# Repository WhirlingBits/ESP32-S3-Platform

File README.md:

# ESP_Platform_Schematic

## Description
Schematics of basic ESP32-S3-WROOM platform with versatile power management
for 12V and 5V supply and microSD card slot.
The board offers 2 USB-C receptables, one connecting to a USB-2-UART converter
(CP2102) feeding the genuine UART0 on ESP32-S3 and another directly connecting
to the ESP32-S3's USB OTG port.

## Power Management
The board may be powered by one of the USB ports (VBUS) or with an external
power supply connected via BarrelJack. So altogether there are 3 possible sources of
power, USB (PGM), USB (Data) and Ext. To prevent any currents flowing from the
source with higher voltage to a source with lower voltage Schotty diodes with
low treshold have been implemented.

Thanx to the buck/boost capability of the LTC3111 used the external power input
voltage may supply a voltage between 3..15V.

Alternatively it is possible to use an external battery controller (e.g. Sparkfun
Babysitter) which is connected on J5 whereas J5.4 (+5VD) will be the input for the
controller and J5.1,2 the output.

## Wifi/BT module from Espressif
For the module we have chosen an ESP32-S3-WROOM-1 from Espressif with 8MByte
serial FLASH and 8MByte PSRAM (suffix -N8R8). ESP32-S3 is more powerful than
classical ESP32-D0WD as its using Dual Core Tensilica LX7 with an augmented 
instruction set supporting low level calculations for CNN processing (tinyML).
For precision of all time related processes there's an clock crystal (32kHz)
assembled.

And this is the real board:

## CAE System
Schematics and Layout have been developed using KiCAD 5.x version. You may
just download the complete repository to a folder inside your KiCAD project
directories to start using it.

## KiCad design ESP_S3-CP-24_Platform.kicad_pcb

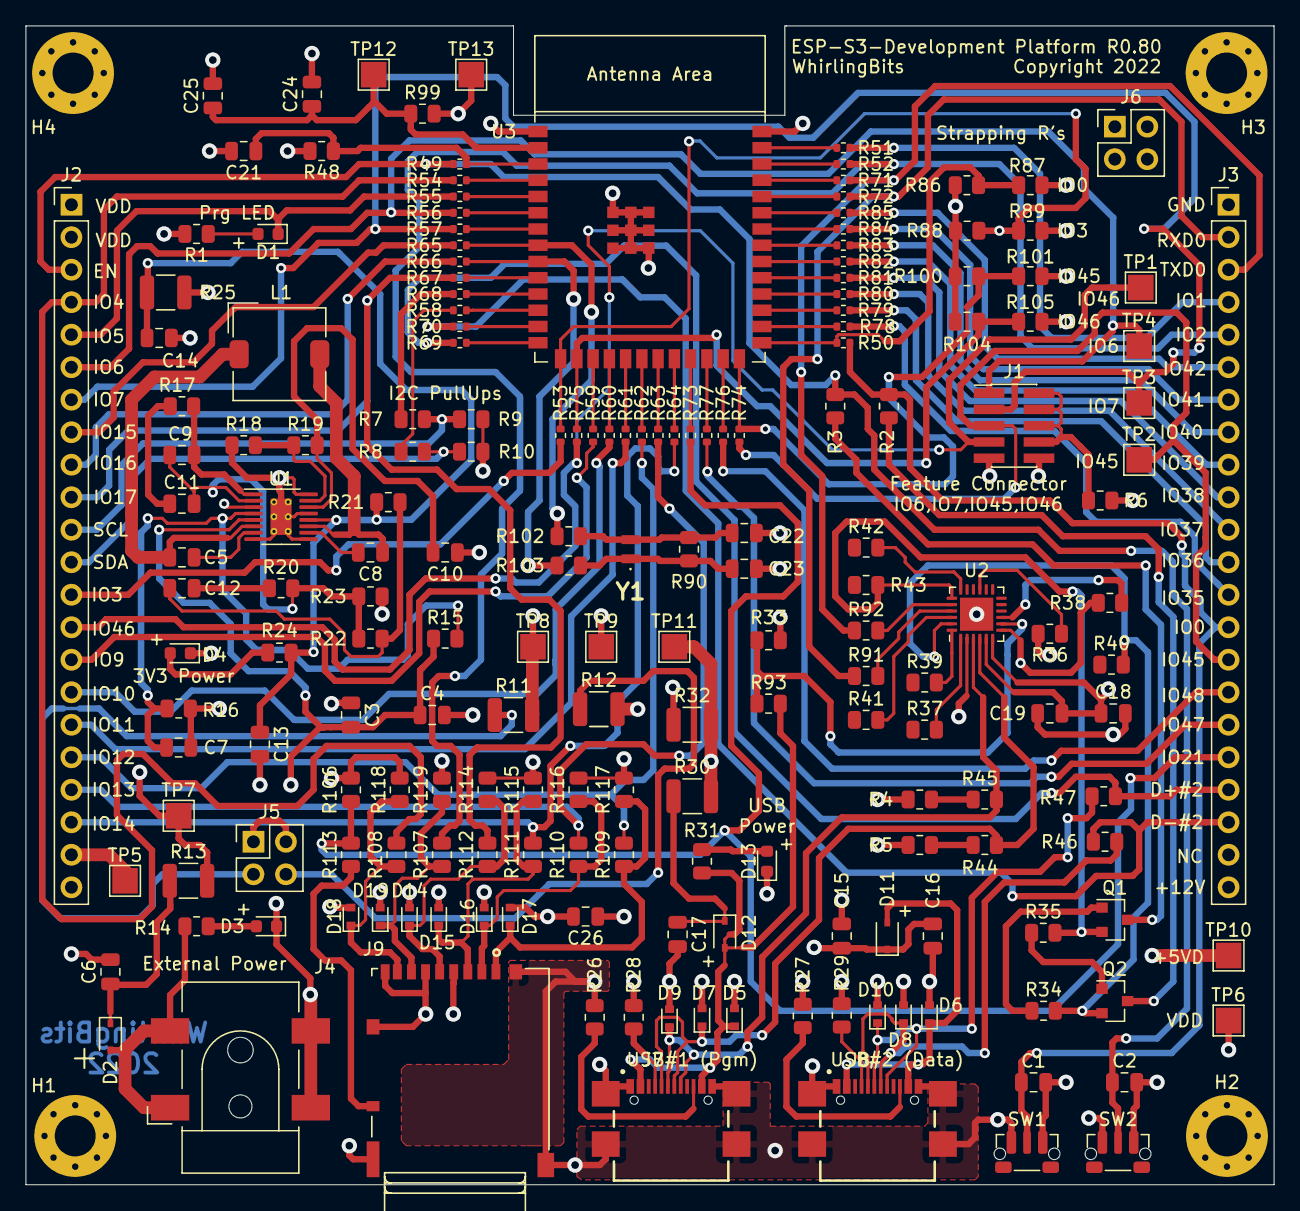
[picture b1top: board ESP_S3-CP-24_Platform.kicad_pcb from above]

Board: 4 copper layers, 97.5 x 90.6 mm, 193 parts (0 on the bottom side), 142 nets.

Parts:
C1: 0.1uF, 50V (DNP); C_0805_2012Metric
C2, C3, C5, C8, C15, C18, C21, C25: 0.1uF, 50V; C_0805_2012Metric
C4, C6: 47uF, 22V; C_0805_2012Metric
C7, C10, C14: 1uF, 16V; C_0805_2012Metric
C9: 22p; C_0805_2012Metric
C11: 1500p; C_0805_2012Metric
C12: 47p; C_0805_2012Metric
C13: 100uF, 6,3V; C_0805_2012Metric
C16, C17, C19: 4.7uF, 25V; C_0805_2012Metric
C22, C23: 12pF, 50V; C_0805_2012Metric
C24, C26: 22uF, 10V; C_0805_2012Metric
D1, D3, D4, D13: LTST-C191KRKT (Red); LED_0603_1608Metric
D2, D11, D12: BAT760-7; D_SOD-323
D5, D6, D7, D8, D9, D10, D14, D15, D16, D17, D18, D19: PESD15VW1BCSFYL; D_SOD-523
H1, H2, H3, H4: M3-L5-3.5; MountingHole_3.2mm_M3_Pad_Via
J1: Conn_02x05_Odd_Even; PinHeader_2x05_P1.27mm_Vertical_SMD
J2, J3: Conn_01x22 (DNP); PinHeader_1x22_P2.54mm_Vertical
J4: PJ-002AH-SMT-TR (Barrel Jack); BarrelJack_CLIFF_FC681465S_SMT_Horizontal
J5: Conn_02x02_Top_Bottom; PinHeader_2x02_P2.54mm_Vertical
J6: Conn_02x02_Top_Bottom (DNP); PinHeader_2x02_P2.54mm_Vertical
J7, J8: USB4110-GF-A_REVB; GCT_USB4110-GF-A_REVB
J9: DM3AT-SF-PEJM5; HRS_DM3AT-SF-PEJM5
L1: 10uH - SLF7032T-100M1R4-2PF; L_TDK_SLF7032
Q1, Q2: SS8050-G; SOT-23
R1: 1k8; R_0805_2012Metric
R2, R3, R6, R7, R8, R19, R37, R39, R40, R41, R42, R43, R91, R92, R99, R102, R103, R107, R108, R109, R110, R111, R112, R113: 0R; R_0805_2012Metric
R4, R5, R16: 1M (DNP); R_0805_2012Metric
R9, R10, R38: 1k; R_0805_2012Metric
R11, R12, R13, R25, R30, R32: 0R1; R_1210_3225Metric
R14, R26, R27, R28, R29, R88, R101: 5k1; R_0805_2012Metric
R15: 1M; R_0805_2012Metric
R17: 41,2k; R_0805_2012Metric
R18: 0R (DNP); R_0805_2012Metric
R20: 11,5k; R_0805_2012Metric
R21: 49R9; R_0805_2012Metric
R22: 845k; R_0805_2012Metric
R23: 261k; R_0805_2012Metric
R24: 1k5; R_0805_2012Metric
R31: 2k2; R_0805_2012Metric
R33: 43k; R_0805_2012Metric
R34, R35, R48, R106, R114, R115, R116, R117, R118, R119: 10k; R_0805_2012Metric
R36: 10k (DNP); R_0805_2012Metric
R44, R45, R46, R47: 22R; R_0805_2012Metric
R49, R50, R51, R52, R53, R54, R55, R56, R57, R58, R59, R60, R61, R62, R63, R64, R65, R66, R67, R68, R69, R70, R71, R72, R73, R74, R75, R76, R77, R78, R79, R80, R81, R82, R83, R84, R85: 22R; R_0402_1005Metric
R86, R87, R89, R100, R104, R105: 5k1 (DNP); R_0805_2012Metric
R90: 5.6M; R_0805_2012Metric
R93: 22k; R_0805_2012Metric
SW1, SW2: SKRTLAE010; SW_Push_1P1T-MP_NO_Horizontal_Alps_SKRTLAE010
TP1: T_IO46; TestPoint_Pad_2.0x2.0mm
TP2: T_IO45; TestPoint_Pad_2.0x2.0mm
TP3: T_IO7; TestPoint_Pad_2.0x2.0mm
TP4: T_IO6; TestPoint_Pad_2.0x2.0mm
TP5: +5VD; TestPoint_Pad_2.0x2.0mm
TP6, TP12: ESP-Power; TestPoint_Pad_2.0x2.0mm
TP7: +12V; TestPoint_Pad_2.0x2.0mm
TP8: Ext Voltage 12V; TestPoint_Pad_2.0x2.0mm
TP9: 3V3; TestPoint_Pad_2.0x2.0mm
TP10: USB Voltage; TestPoint_Pad_2.0x2.0mm
TP11: USB Vltge #2; TestPoint_Pad_2.0x2.0mm
TP13: VDD33; TestPoint_Pad_2.0x2.0mm
U1: LTC3111EMSEPBF; MSOP-16-1EP_3x4.039mm_P0.5mm_EP1.651x2.845mm_ThermalVias
U2: CP2102N-A02-GQFN24; QFN-24-1EP_4x4mm_P0.5mm_EP2.6x2.6mm
U3: ESP32-S3-WROOM-1
Y1: XTAL 32,678kHz (C20S-12.5PF20PPM); SC20S125PF20PPM

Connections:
+5VD: J2.21, R12.2, R30.2, R32.2, TP5.1, TP10.1, TP11.1
+12V: J3.22, R11.2, R13.2, TP7.1, TP8.1
/CP_EN: Q1.3, R3.2
/CP_IO0: Q2.3, R2.2
/Espressif Developer PLatform - uSDCard/SD_DET: J9.SWA, R113.1
/Espressif Developer PLatform - uSDCard/SD_HOST_CLK: D14.1, J9.5, R112.1, R114.1
/Espressif Developer PLatform - uSDCard/SD_HOST_CMD: D15.1, J9.3, R111.1, R115.1
/Espressif Developer PLatform - uSDCard/SD_HOST_D0: D19.1, J9.7, R107.1, R119.1
/Espressif Developer PLatform - uSDCard/SD_HOST_D1: D18.1, J9.8, R108.1, R118.1
/Espressif Developer PLatform - uSDCard/SD_HOST_D2: D17.1, J9.1, R109.1, R117.1
/Espressif Developer PLatform - uSDCard/SD_HOST_D3: D16.1, J9.2, R110.1, R116.1
/Espressif Developer Platform - Interfaces/USB-D+#2: D10.1, J8.A6, J8.B6, R47.2
/Espressif Developer Platform - Interfaces/USB-D-#2: D8.1, J8.A7, J8.B7, R46.2
/Espressif Developer Platform - Interfaces/USB_VBUS#2: D6.1, D11.2, J8.A4/B9, J8.B4/A9
/Espressif Developer Platform - Modules/32K_XN: R66.1, R103.1, U3.9
/Espressif Developer Platform - Modules/32K_XP: R65.1, R102.1, U3.8
/Espressif Developer Platform - Modules/ESP-Power: C24.1, C25.1, R99.1, TP12.1, U3.2
/Espressif Developer Platform - Modules/ESP_EN: C21.1, R48.1, R49.1, U3.3
/Espressif Developer Platform - Modules/IO_0: R50.1, R86.1, R87.2, U3.27
/Espressif Developer Platform - Modules/IO_1: R51.1, U3.39
/Espressif Developer Platform - Modules/IO_2: R52.1, U3.38
/Espressif Developer Platform - Modules/IO_3: R53.1, R88.1, R89.2, U3.15
/Espressif Developer Platform - Modules/IO_4: R54.1, U3.4
/Espressif Developer Platform - Modules/IO_5: R55.1, U3.5
/Espressif Developer Platform - Modules/IO_6: R56.1, U3.6
/Espressif Developer Platform - Modules/IO_7: R57.1, U3.7
/Espressif Developer Platform - Modules/IO_8: R58.1, U3.12
/Espressif Developer Platform - Modules/IO_9: R59.1, U3.17
/Espressif Developer Platform - Modules/IO_10: R60.1, U3.18
/Espressif Developer Platform - Modules/IO_11: R61.1, U3.19
/Espressif Developer Platform - Modules/IO_12: R62.1, U3.20
/Espressif Developer Platform - Modules/IO_13: R63.1, U3.21
/Espressif Developer Platform - Modules/IO_14: R64.1, U3.22
/Espressif Developer Platform - Modules/IO_17: R67.1, U3.10
/Espressif Developer Platform - Modules/IO_18: R68.1, U3.11
/Espressif Developer Platform - Modules/IO_21: R73.2, U3.23
/Espressif Developer Platform - Modules/IO_35: R78.2, U3.28
/Espressif Developer Platform - Modules/IO_36: R79.2, U3.29
/Espressif Developer Platform - Modules/IO_37: R80.2, U3.30
/Espressif Developer Platform - Modules/IO_38: R81.2, U3.31
/Espressif Developer Platform - Modules/IO_39: R82.2, U3.32
/Espressif Developer Platform - Modules/IO_40: R83.2, U3.33
/Espressif Developer Platform - Modules/IO_41: R84.2, U3.34
/Espressif Developer Platform - Modules/IO_42: R85.2, U3.35
/Espressif Developer Platform - Modules/IO_45: R74.2, R100.1, R101.2, U3.26
/Espressif Developer Platform - Modules/IO_46: R75.2, R104.1, R105.2, U3.16
/Espressif Developer Platform - Modules/IO_47: R77.2, U3.24
/Espressif Developer Platform - Modules/IO_48: R76.2, U3.25
/Espressif Developer Platform - Modules/RXD0: R72.2, U3.36
/Espressif Developer Platform - Modules/TXD0: R71.2, U3.37
/Espressif Developer Platform - Modules/USB_D+#2: R69.2, U3.14
/Espressif Developer Platform - Modules/USB_D-#2: R70.2, U3.13
/Espressif Developer Platform - Power/J5_5V: J5.4, R12.1
/Espressif Developer Platform - Power/J5_12V: J5.3, R11.1
/Espressif Developer Platform - Power/LT_COMP: C9.1, R17.2, U1.1
/Espressif Developer Platform - Power/LT_FB: C9.2, C11.2, R20.2, R22.2, R23.1, U1.2
/Espressif Developer Platform - Power/LT_PWM: R18.2, R19.1, U1.15
/Espressif Developer Platform - Power/LT_RUN: C7.2, R15.2, R16.1, U1.4
/Espressif Developer Platform - Power/LT_VCC: C10.2, R19.2, U1.14
/Espressif Developer Platform - Power/LT_VIN: C3.2, C4.1, J5.1, J5.2, R15.1, U1.5
/Espressif Developer Platform - USB-Converter/CP_CTS: R42.2, U2.18
/Espressif Developer Platform - USB-Converter/CP_DCD: R39.2, U2.24
/Espressif Developer Platform - USB-Converter/CP_DSR: R41.2, U2.22
/Espressif Developer Platform - USB-Converter/CP_DTR: Q2.2, R34.2, R40.2, U2.23
/Espressif Developer Platform - USB-Converter/CP_RI: R37.2, U2.1
/Espressif Developer Platform - USB-Converter/CP_RST: R38.1, U2.9
/Espressif Developer Platform - USB-Converter/CP_RTS: Q1.2, R35.2, R43.2, U2.19
/Espressif Developer Platform - USB-Converter/CP_RXD: R92.2, U2.20
/Espressif Developer Platform - USB-Converter/CP_TXD: R91.2, U2.21
/Espressif Developer Platform - USB-Converter/CP_VBUS: R33.2, R93.1, U2.8
/I2C_SCL: J2.11, R7.1, R9.1
/I2C_SDA: J2.12, R8.1, R10.1
/R_EN: C2.1, J2.3, R3.1, R49.2, SW2.2
/R_IO0: C1.1, J3.14, R2.1, R50.2, SW1.2
/R_IO1: J3.4, R51.2
/R_IO2: J3.5, R52.2, R107.2
/R_IO3: J2.13, R53.2
/R_IO4: J2.4, R54.2, R108.2
/R_IO5: D1.1, J2.5, R55.2
/R_IO6: J1.1, J2.6, R56.2, TP4.1
/R_IO7: J1.3, J2.7, R57.2, TP3.1
/R_IO8: R8.2, R58.2
/R_IO9: J2.15, R59.2
/R_IO10: J2.16, R60.2
/R_IO11: J2.17, R61.2
/R_IO12: J2.18, R62.2, R109.2
/R_IO13: J2.19, R63.2, R110.2
/R_IO14: J2.20, R64.2, R111.2
/R_IO15: J2.8, R65.2
/R_IO16: J2.9, R66.2
/R_IO17: J2.10, R67.2, R112.2
/R_IO18: R7.2, R68.2
/R_IO21: J3.18, R73.1, R106.1, R113.2
/R_IO35: J3.13, R78.1
/R_IO36: J3.12, R79.1
/R_IO37: J3.11, R80.1
/R_IO38: J3.10, R81.1
/R_IO39: J3.9, R82.1
/R_IO40: J3.8, R83.1
/R_IO41: J3.7, R84.1
/R_IO42: J3.6, R85.1
/R_IO45: J1.5, J3.15, R74.1, TP2.1
/R_IO46: J1.7, J2.14, R75.1, TP1.1
/R_IO47: J3.17, R77.1
/R_IO48: J3.16, R76.1
/R_RXD0: J3.2, R72.1, R91.1
/R_TXD0: J3.3, R71.1, R92.1
/R_USB-D+#1: R4.2, R45.1
/R_USB-D+#2: J3.19, R47.1, R69.1
/R_USB-D-#1: R5.2, R44.1
/R_USB-D-#2: J3.20, R46.1, R70.1
/USB-D+#1: D9.1, J7.A6, J7.B6, R45.2, U2.3
/USB-D-#1: D7.1, J7.A7, J7.B7, R44.2, U2.4
GND: C1.2, C2.2, C3.1, C4.2, C6.2, C7.1, C10.1, C13.2, C14.1, C15.2, C16.2, C17.2, C18.2, C19.2, C21.2, C22.2, C23.2, C24.2, C25.2, C26.2, D3.1, D4.1, D5.2, D6.2, D7.2, D8.2, D9.2, D10.2, D13.1, D14.2, D15.2, D16.2, D17.2, D18.2, D19.2, H1.1, H2.1, H3.1, H4.1, J1.9, J1.10, J2.22, J3.1, J4.2, J4.3, J6.3, J6.4, J7.A1/B12, J7.B1/A12, J7.S1, J7.S2, J7.S3, J7.S4, J8.A1/B12, J8.B1/A12, J8.S1, J8.S2, J8.S3, J8.S4, J9.6, J9.P1, J9.P2, J9.P3, J9.P4, J9.SWB, R4.1, R5.1, R16.2, R18.1, R23.2, R26.1, R27.1, R28.1, R29.1, R33.1, R36.2, R87.1, R89.1, R101.1, R105.1, SW1.1, SW1.3, SW2.1, SW2.3, U1.3, U1.8, U1.9, U1.13, U1.16, U1.17, U2.2, U2.25, U3.1, U3.40, U3.41
unnamed: C5.1, L1.1, U1.6
unnamed: C5.2, U1.7
unnamed: C6.1, D2.1, R13.1
unnamed: C8.1, L1.2, U1.11
unnamed: C8.2, U1.10
unnamed: C11.1, R17.1
unnamed: C12.1, R20.1
unnamed: C12.2, R21.2, R22.1
unnamed: C13.1, C14.2, R21.1, R24.2, R25.1, U1.12
unnamed: C15.1, C16.1, D11.1, R32.1
unnamed: C17.1, D12.1, R30.1
unnamed: C22.1, R90.2, R102.2, Y1.2
unnamed: C23.1, R90.1, R103.2, Y1.1
unnamed: D1.2, R1.1
unnamed: D2.2, J4.1, R14.2
unnamed: D3.2, R14.1
unnamed: D4.2, R24.1
unnamed: D13.2, R31.1
unnamed: J1.2, J1.4, J1.6, J1.8, R6.1
unnamed: J7.A5, R28.2
unnamed: J7.B5, R26.2
unnamed: J8.A5, R29.2
unnamed: J8.B5, R27.2
unnamed: Q1.1, R34.1
unnamed: Q2.1, R35.1
unnamed: R36.1, U2.15
VBUS: D5.1, D12.2, J7.A4/B9, J7.B4/A9, R31.2, R93.2
VDD: C18.1, C19.1, C26.1, J2.1, J2.2, J6.1, J6.2, J9.4, R1.2, R6.2, R9.2, R10.2, R25.2, R38.2, R48.2, R86.2, R88.2, R99.2, R100.2, R104.2, R106.2, R114.2, R115.2, R116.2, R117.2, R118.2, R119.2, TP6.1, TP9.1, TP13.1, U2.5, U2.6, U2.7

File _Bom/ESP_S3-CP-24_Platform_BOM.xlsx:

ESP-S3 Developer Platform R0.80 (12.3.2022)
Pos | Sourced | References | Value | Footprint | DigiKey | LCSC | Mouser | Quantity
1 |  | C2, C3, C5, C8, C15, C18, C21, C25 | 0.1uF, 50V | C_0805_2012Metric |  | C161260 |  | 8
2 |  | C7, C10, C14 | 1uF, 16V | C_0805_2012Metric |  | C16834 |  | 3
3 |  | C16, C17, C19 | 4.7uF, 25V | C_0805_2012Metric |  | C98192 |  | 3
4 |  | C4, C6 | 47uF, 22V | C_0805_2012Metric |  | C913559 |  | 2
5 |  | C22, C23 | 12pF, 50V | C_0805_2012Metric |  | C182488 |  | 2
6 |  | C24, C26 | 22uF, 10V | C_0805_2012Metric |  | C77074 |  | 2
7 |  | C1 | 0.1uF, 50V (DNP) | C_0805_2012Metric |  | C161260 |  | 1
8 |  | C9 | 22p | C_0805_2012Metric |  | C105623 |  | 1
9 |  | C11 | 1500p | C_0805_2012Metric |  | C114765 |  | 1
10 |  | C12 | 47p | C_0805_2012Metric |  | C113821 |  | 1
11 |  | C13 | 100uF, 6,3V | C_0805_2012Metric |  | C141660 |  | 1
12 |  | R49, R50, R51, R52, R53, R54, R55, R56, R57, R58, R59, R60, R61, R62, R63, R64,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 | 22R | R_0402_1005Metric |  | C114765 |  | 37
13 |  | R2, R3, R6, R7, R8, R19, R37, R39, R40, R41, R42, R43, R91, R92, R99, R102, R10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 | 0R | R_0805_2012Metric |  | C100045 |  | 24
14 |  | R34, R35, R48, R106, R114, R115, R116, R117, R118, R119 | 10k | R_0805_2012Metric |  | C169253 |  | 10
15 |  | R14, R26, R27, R28, R29, R88, R101 | 5k1 | R_0805_2012Metric |  | C204548 |  | 7
16 |  | R11, R12, R13, R25, R30, R32 | 0R1 | R_1210_3225Metric |  | C473589 |  | 6
17 |  | R86, R87, R89, R100, R104, R105 | 5k1 (DNP) | R_0805_2012Metric |  | C204548 |  | 6
18 |  | R44, R45, R46, R47 | 22R | R_0805_2012Metric |  | C144531 |  | 4
19 |  | R4, R5, R16 | 1M (DNP) | R_0805_2012Metric |  | C230655 |  | 3
20 |  | R9, R10, R38 | 1k | R_0805_2012Metric |  | C95781, |  | 3
21 |  | R1 | 1k8 | R_0805_2012Metric |  | C137465 |  | 1
22 |  | R15 | 1M | R_0805_2012Metric |  | C230655 |  | 1
23 |  | R17 | 41,2k | R_0805_2012Metric |  | C204486 |  | 1
24 |  | R18 | 0R (DNP) | R_0805_2012Metric |  | C100045 |  | 1
25 |  | R20 | 11,5k | R_0805_2012Metric |  | C228269 |  | 1
26 |  | R21 | 49R9 | R_0805_2012Metric |  | C479104 |  | 1
27 |  | R22 | 845k | R_0805_2012Metric |  | C416871 |  | 1
28 |  | R23 | 270k | R_0805_2012Metric |  | C352236 |  | 1
29 |  | R24 | 1k5 | R_0805_2012Metric |  | C163951 |  | 1
30 |  | R31 | 2k2 | R_0805_2012Metric |  | C441982 |  | 1
31 |  | R33 | 47.5k | R_0805_2012Metric |  | C104355 |  | 1
32 |  | R36 | 10k (DNP) | R_0805_2012Metric |  |  |  | 1
33 |  | R90 | 5.6M | R_0805_2012Metric |  | C185285 |  | 1
34 |  | R93 | 22.1k | R_0805_2012Metric |  | C104113 |  | 1
35 |  | L1 | 10uH - SLF7032T-100M1R4-2PF | L_TDK_SLF7032 |  | C76852 |  | 1
36 |  | D5, D6, D7, D8, D9, D10, D14, D15, D16, D17, D18, D19 | PESD15VW1BCSFYL | D_SOD-523 |  |  | 771-PESD15VW1BCSFYL | 12
37 |  | D1, D3, D4, D13 | LTST-C191KRKT (Red) | LED_0603_1608Metric |  | C125099 |  | 4
38 |  | D2, D11, D12 | BAT760-7 | D_SOD-323 |  | C116158 |  | 3
39 |  | U1 | LTC3111EMSEPBF | MSOP-16 |  | C684080 | 584-LTC3111EMSETRPBF | 1
40 |  | U2 | CP2102N-A02-GQFN24 | QFN-24-1EP_4x4mm_P0.5mm_EP2.6x2.6mm |  | C80225 |  | 1
41 |  | U3 | ESP32-S3-WROOM-1 | ESP32-S3-WROOM-1 |  | C2913201 |  | 1
42 |  | Y1 | XTAL 32,678kHz (C20S-12.5PF20PPM) | SC20S125PF20PPM |  | C97603 |  | 1
43 |  | SW1, SW2 | SKRTLAE010 | SW_Push_1P1T-MP_NO_Horizontal_Alps_SKRTLAE010 |  | C110293 |  | 2
44 |  | Q1, Q2 | SS8050-G | SOT-23 |  | C164885 |  | 2
45 |  | J2, J3 | Conn_01x22 (DNP) | PinHeader_1x22_P2.54mm_Vertical |  | C725954 |  | 2
46 |  | J5, J6 | Conn_02x02_Top_Bottom (DNP) | PinHeader_2x02_P2.54mm_Vertical |  | C492419 |  | 2
47 |  | J7, J8 | USB_C_Receptacle (USB4110-GF-A) | GCT_USB4110-GF-A_REVB |  |  | 640-USB4110-GF-A | 2
48 |  | J1 | Conn_02x05_Odd_Even | PinHeader_2x05_P1.27mm_Vertical_SMD |  | C150517 |  | 1
49 |  | J4 | PJ-002AH-SMT-TR (Barrel Jack) | BarrelJack_CLIFF_FC681465S_SMT_Horizontal |  |  | 490-PJ-002AH-SMT-TR | 1
50 |  | J9 | DM3AT-SF-PEJM5 | HRS_DM3AT-SF-PEJM5 |  | C114218 |  | 1

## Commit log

2022-04-04 Create LICENSE
2022-04-04 Initial Release

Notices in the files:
ESP_S3-CP-24_Platform.kicad_pcb:
Copyright 2022
